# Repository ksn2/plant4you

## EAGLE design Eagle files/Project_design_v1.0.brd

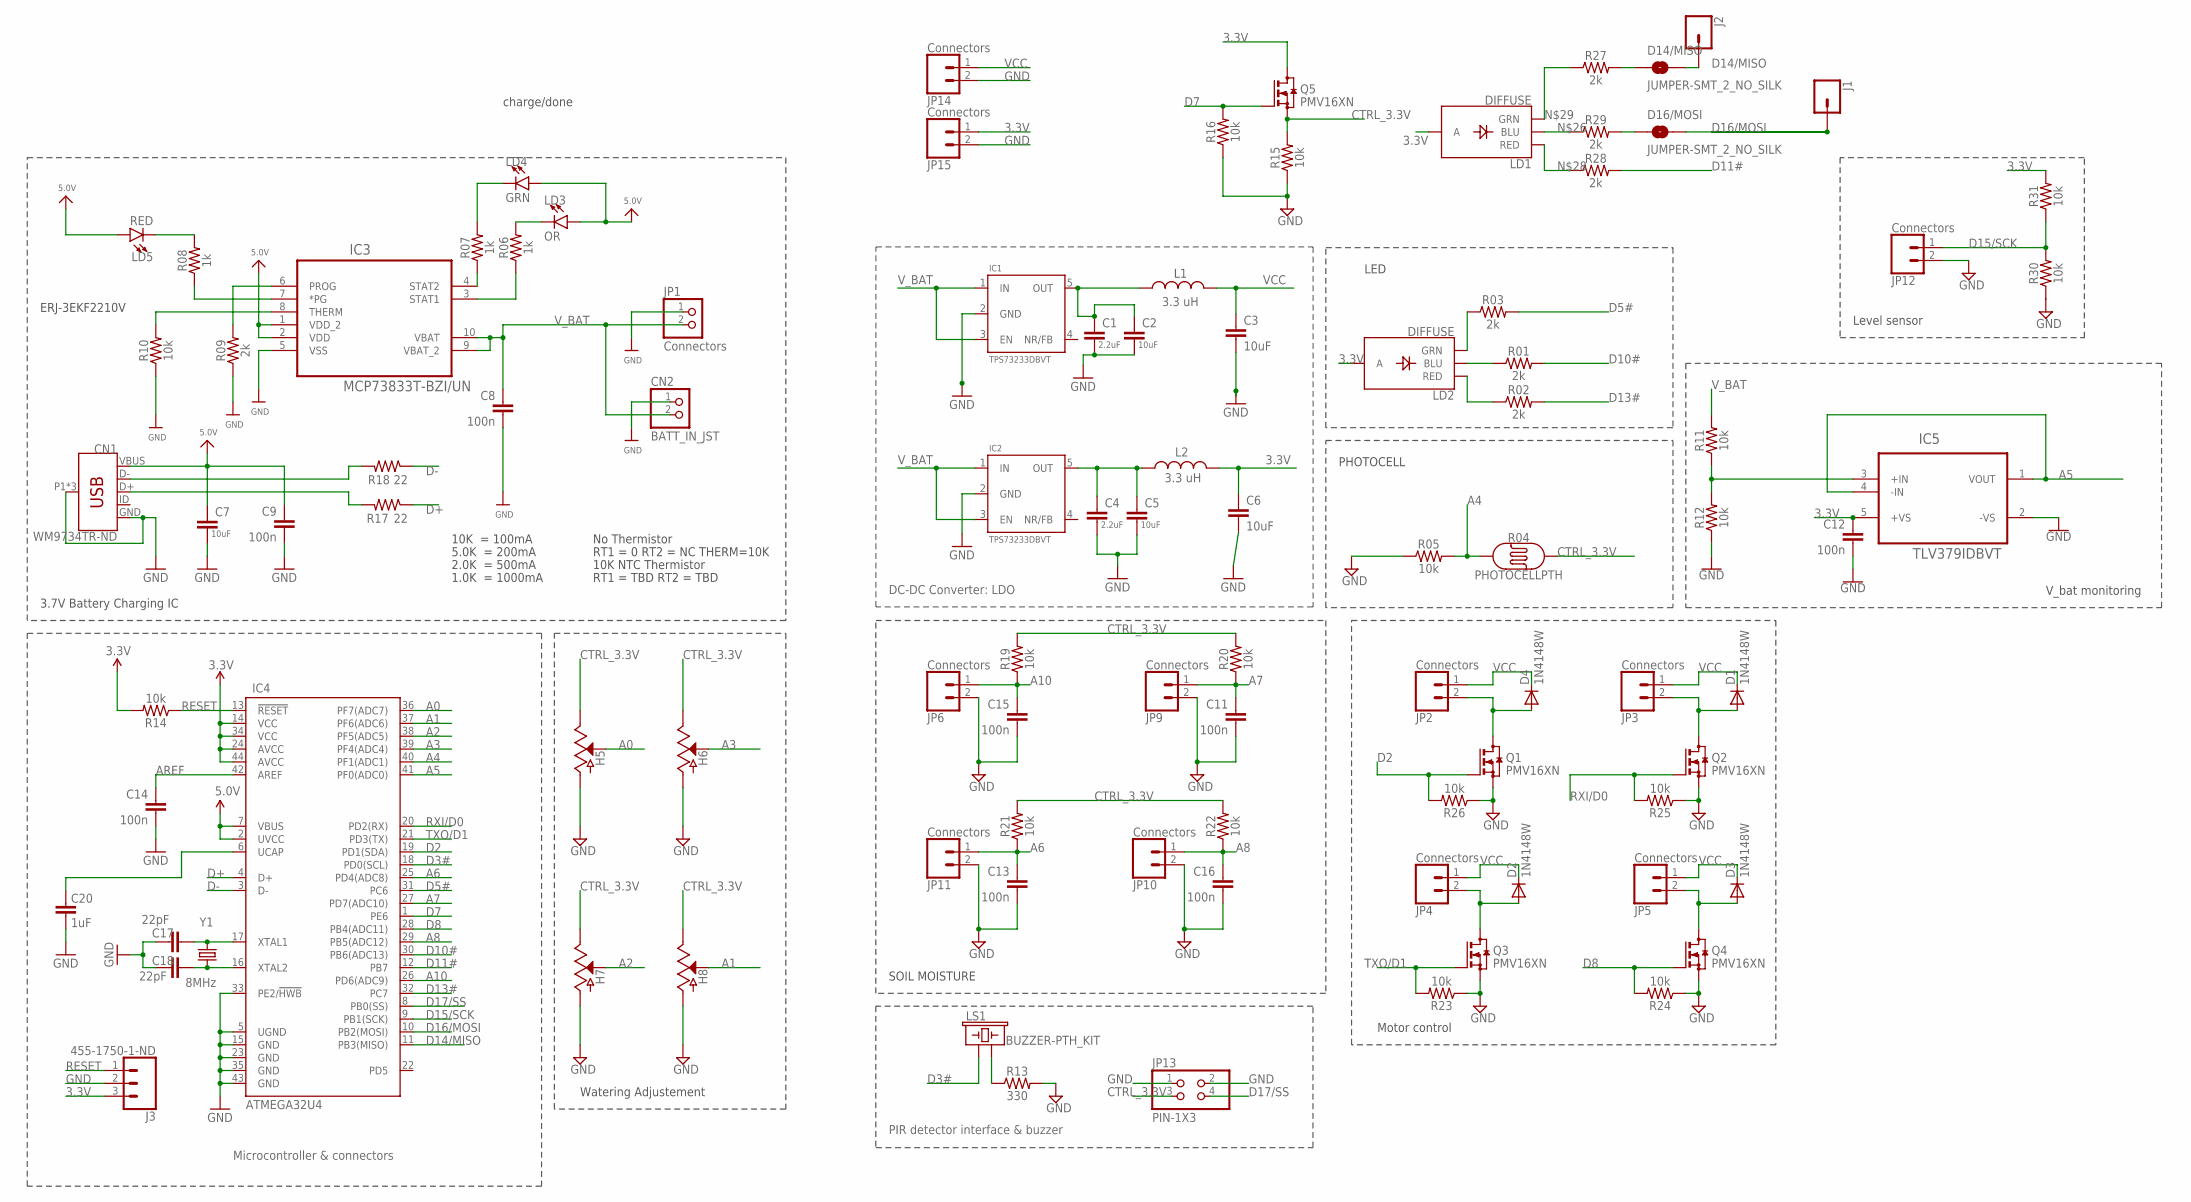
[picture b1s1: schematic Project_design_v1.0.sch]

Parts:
C1, C4: 2.2uF; 0603-CAP; PARTNO C1608X7S1C225K080AC
C2, C3, C5, C6, C7: 10uF; 0603-CAP; PARTNO GRM188R60J106ME47D
C8, C9, C11, C12, C13, C14, C15, C16: 100n; 0402; PARTNO CGA2B3X7R1E104K050BB
C17, C18: 22pF; 0603-CAP; PARTNO CL10C2R2BB8NNNC
C20: 1uF; 0603-CAP; PARTNO CL10B105KP8NNNC
CN1: WM9734TR-ND; USB-B-MICRO-SMD_VERT; PARTNO 1051330011
CN2: BATT_IN_JST; JSTPH2; PARTNO B2B-XH-A(LF)(SN)
D1, D2, D3, D4: 1N4148W; SOD-123_MINI-SMA; PARTNO 1N4148W
D14/MISO, D16/MOSI: JUMPER-SMT_2_NO_SILK; SMT-JUMPER_2_NO_SILK
H5: POT1; SOIL_MOISTURE; PARTNO SEN-13322
H6: POT2; SOIL_MOISTURE; PARTNO SEN-13322
H7: POT3; SOIL_MOISTURE; PARTNO SEN-13322
H8: POT4; SOIL_MOISTURE; PARTNO SEN-13322
IC1, IC2: TPS73233DBVT; SOT23-5; PARTNO TPS73233DBVT
IC3: MCP73833T-BZI/UN; SOP50P490X110-10N
IC4: ATMEGA32U4; TQFP44; PARTNO ATMEGA32U4RC-MUR
IC5: TLV379IDBVT; SOT95P280X145-5N; PARTNO TLV379IDBVT
J1, J2: CONN_01; 1X01
J3: 455-1750-1-ND; 1X03
JP1: Connectors; 1X02; PARTNO /
JP2, JP3, JP4, JP5, JP6, JP9, JP10, JP11, JP12, JP14, JP15: Connectors; 1X02; PARTNO M20-9960245
JP13: PIN-1X3; 2X02; PARTNO M22-2040805
L1, L2: 3.3 uH; 0603; PARTNO LQM18PN3R3MGHD
LD1, LD2: DIFFUSE; LED-RGB_THRU_5MM; PARTNO WP154A4SEJ3VBDZGW/CA
LD3: OR; LED_3MM; PARTNO TLHO4600
LD4: GRN; LED_3MM; PARTNO TLLG4400
LD5: RED; LED_3MM; PARTNO TLHK4600
LS1: BUZZER-PTH_KIT; BUZZER-12MM-KIT; PARTNO CEM-1203(42)
Q1, Q2, Q3, Q4, Q5: PMV16XN; SOT23; PARTNO PMV16XNR
R01, R02, R03, R09, R27, R28, R29: 2k; 0603; PARTNO ERJ-PA3F2001V
R04: PHOTOCELLPTH; PHOTOCELL; PARTNO 1528-2141-ND
R05, R10, R11, R12, R14, R15, R16, R19, R20, R21, R22, R23, R24, R25, R26, R30, R31: 10k; 0603; PARTNO ERA-3AEB103V
R06, R07, R08: 1k; 0603; PARTNO RC0603JR-07330RL
R13: 330; 0603; PARTNO RC0603JR-07330RL
R17, R18: 22; 0603-RES; PARTNO RC0603JR-0722RL
Y1: 8MHz; CRYSTAL-SMD-5X3; PARTNO ABM3C-8.000MHZ-D4Y-T

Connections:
3.3V: C6.1, C12.1, IC4.14 (VCC), IC4.24 (AVCC), IC4.34 (VCC), IC4.44 (AVCC), IC5.5 (+VS), J3.3, JP15.1, L2.2, LD1.3 (A), LD2.3 (A), Q5.3 (D), R14.2, R31.2
5.0V: C7.1, C9.1, CN1.VBUS, IC3.1 (VDD_2), IC3.2 (VDD), IC4.2 (UVCC), IC4.7 (VBUS), LD3.A, LD4.A, LD5.A
A0: H5.3 (VOUT), IC4.36 (PF7(ADC7))
A1: H8.3 (VOUT), IC4.37 (PF6(ADC6))
A2: H7.3 (VOUT), IC4.38 (PF5(ADC5))
A3: H6.3 (VOUT), IC4.39 (PF4(ADC4))
A4: IC4.40 (PF1(ADC1)), R04.1, R05.2
A5: IC4.41 (PF0(ADC0)), IC5.1 (VOUT), IC5.4 (-IN)
A6: C13.1, IC4.25 (PD4(ADC8)), JP11.1, R21.1
A7: C11.1, IC4.27 (PD7(ADC10)), JP9.1, R20.1
A8: C16.1, IC4.29 (PB5(ADC12)), JP10.1, R22.1
A10: C15.1, IC4.26 (PD6(ADC9)), JP6.1, R19.1
AREF: C14.1, IC4.42 (AREF)
CTRL_3.3V: H5.1 (VCC), H6.1 (VCC), H7.1 (VCC), H8.1 (VCC), JP13.3, Q5.2 (S), R04.2, R15.2, R19.2, R20.2, R21.2, R22.2
D2: IC4.19 (PD1(SDA)), Q1.1 (G), R26.2
D3#: IC4.18 (PD0(SCL)), LS1.+ (1)
D5#: IC4.31 (PC6), R03.2
D7: IC4.1 (PE6), Q5.1 (G), R16.2
D8: IC4.28 (PB4(ADC11)), Q4.1 (G), R24.2
D10#: IC4.30 (PB6(ADC13)), R01.2
D11#: IC4.12 (PB7), R28.2
D13#: IC4.32 (PC7), R02.2
D14/MISO: D14/MISO.2, IC4.11 (PB3(MISO)), J2.1
D15/SCK: IC4.9 (PB1(SCK)), JP12.1, R30.2, R31.1
D16/MOSI: D16/MOSI.2, IC4.10 (PB2(MOSI)), J1.1
D17/SS: IC4.8 (PB0(SS)), JP13.4
D+: IC4.4 (D+), R17.1
D-: IC4.3 (D-), R18.1
GND: C1.2, C2.2, C3.2, C4.2, C5.2, C6.2, C7.2, C8.2, C9.2, C11.2, C12.2, C13.2, C14.2, C15.2, C16.2, C17.2, C18.2, C20.1, CN1.GND, CN1.P1 (SHIELD), CN1.P2 (SHIELD), CN1.P3 (SHIELD), CN2.1, H5.2 (GND), H6.2 (GND), H7.2 (GND), H8.2 (GND), IC1.2 (GND), IC2.2 (GND), IC3.5 (VSS), IC4.5 (UGND), IC4.15 (GND), IC4.23 (GND), IC4.33 (PE2/!HWB), IC4.35 (GND), IC4.43 (GND), IC5.2 (-VS), J3.2, JP1.1, JP6.2, JP9.2, JP10.2, JP11.2, JP12.2, JP13.1, JP13.2, JP14.2, JP15.2, Q1.2 (S), Q2.2 (S), Q3.2 (S), Q4.2 (S), R05.1, R09.1, R10.1, R12.1, R13.2, R15.1, R16.1, R23.1, R24.1, R25.1, R26.1, R30.1
unnamed: LD2.2 (GRN), R03.1
unnamed: C4.1, C5.1, IC2.5 (OUT), L2.1
unnamed: LD3.K (C), R06.2
unnamed: LD4.K (C), R07.2
unnamed: IC3.4 (STAT2), R07.1
unnamed: IC3.3 (STAT1), R06.1
unnamed: IC3.7 (*PG), R08.1
unnamed: IC3.8 (THERM), R10.2
unnamed: C18.1, IC4.16 (XTAL2), Y1.1
unnamed: D4.A, JP2.2, Q1.3 (D)
unnamed: D1.A, JP3.2, Q2.3 (D)
unnamed: LD5.K (C), R08.2
unnamed: C1.1, C2.1, IC1.5 (OUT), L1.1
unnamed: D2.A, JP4.2, Q3.3 (D)
unnamed: D3.A, JP5.2, Q4.3 (D)
unnamed: IC3.6 (PROG), R09.2
unnamed: IC5.3 (+IN), R11.1, R12.2
unnamed: C17.1, IC4.17 (XTAL1), Y1.3 (2)
unnamed: C20.2, IC4.6 (UCAP)
unnamed: CN1.D-, R18.2
unnamed: CN1.D+, R17.2
unnamed: LS1.- (2), R13.1
unnamed: LD1.1 (BLU), R29.1
unnamed: LD1.4 (RED), R28.1
unnamed: LD1.2 (GRN), R27.1
unnamed: D16/MOSI.1, R29.2
unnamed: D14/MISO.1, R27.2
unnamed: LD2.1 (BLU), R01.1
unnamed: LD2.4 (RED), R02.1
RESET: IC4.13 (!RESET), J3.1, R14.1
RXI/D0: IC4.20 (PD2(RX)), Q2.1 (G), R25.2
TXO/D1: IC4.21 (PD3(TX)), Q3.1 (G), R23.2
VCC: C3.1, D1.C, D2.C, D3.C, D4.C, JP2.1, JP3.1, JP4.1, JP5.1, JP14.1, L1.2
V_BAT: C8.1, CN2.2, IC1.1 (IN), IC1.3 (EN), IC2.1 (IN), IC2.3 (EN), IC3.9 (VBAT_2), IC3.10 (VBAT), JP1.2, R11.2

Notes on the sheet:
LED
PHOTOCELL
SOIL MOISTURE
DC-DC Converter: LDO
10K = 100mA
5.0K = 200mA
2.0K = 500mA
1.0K = 1000mA
No Thermistor
RT1 = 0 RT2 = NC THERM=10K
10K NTC Thermistor
RT1 = TBD RT2 = TBD
3.7V Battery Charging IC
charge/done
Motor control
Level sensor
ERJ-3EKF2210V
Watering Adjustement
V_bat monitoring
Microcontroller & connectors
PIR detector interface & buzzer

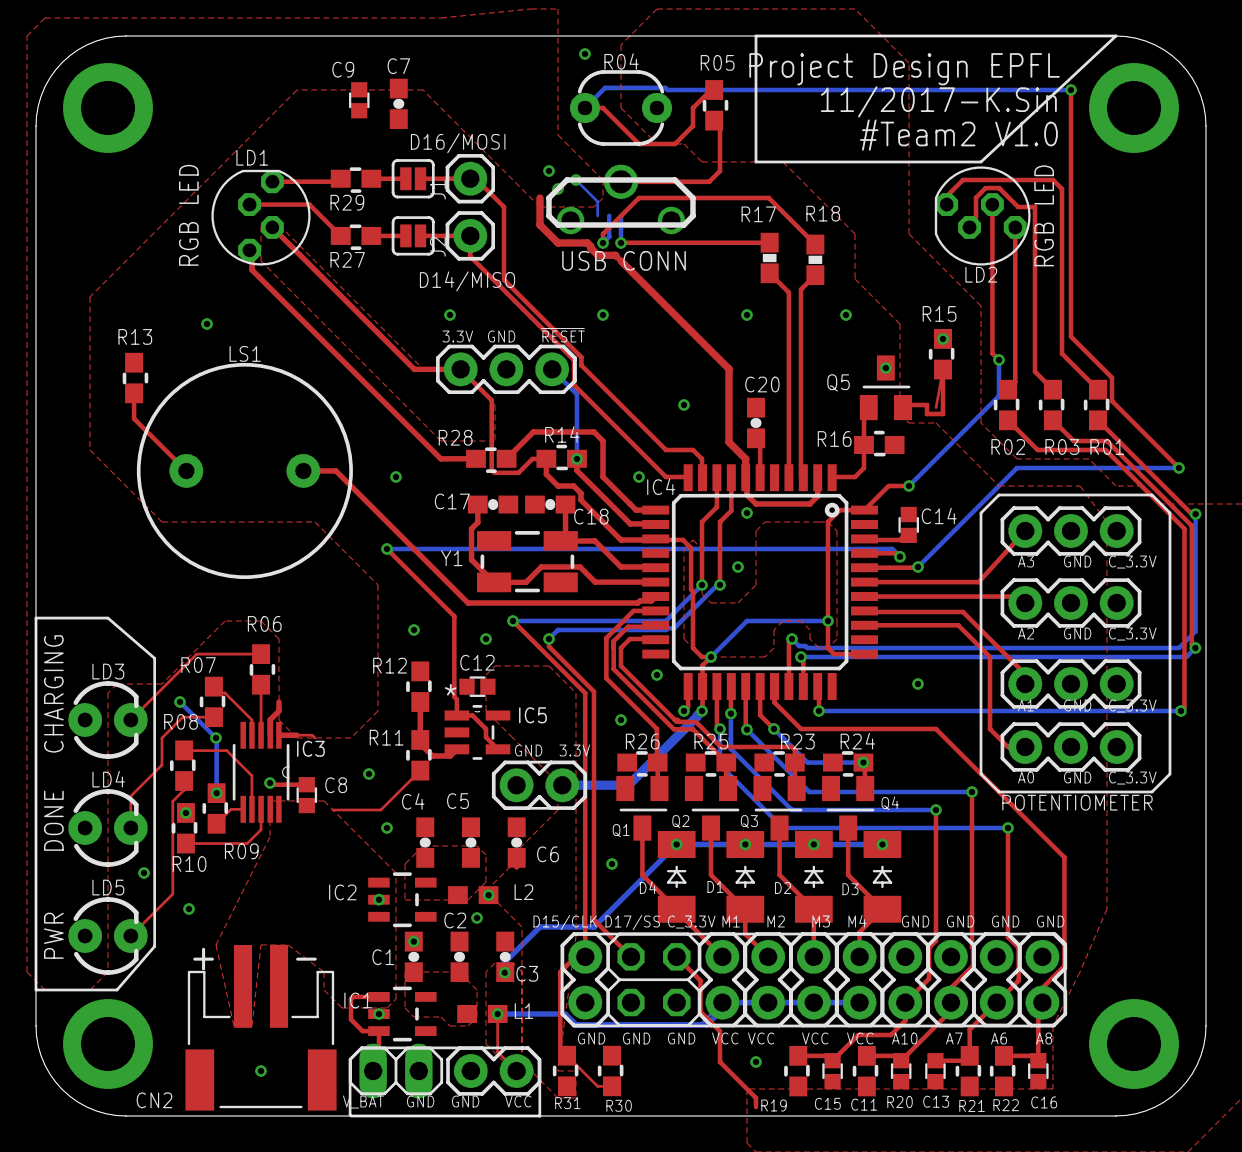
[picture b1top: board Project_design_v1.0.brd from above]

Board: 2 copper layers, 65.0 x 60.0 mm, 96 parts (1 on the bottom side), 63 nets.

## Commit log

2017-10-27 test
2017-10-27 doc de bellouard
2017-10-27 test2
2017-10-27 clean repository
2017-10-27 add readme
2017-10-27 eagle first schemattic;template for futur use
2017-10-30 passif components liste
2017-11-02 first arduino sketch added to control the birghtness of 1 LED
2017-11-02 code to drive a RGB LED added
2017-11-02 Guidelines for midterm presentation deleted
2017-11-02 Photocell code & Fading diode feedback
2017-11-02 Folder edited for the photocell project
2017-11-02 schematic des temperature, soil moisture, led, brightness sensor
2017-11-04 First arduino for the whole project: moisture sensors & motor;LEDs;analog reading of the birghtness sensor
2017-11-07 temperature sensor schmetatic & packages edited
2017-11-08 arduino code updated & correcter
2017-11-09 MCU, charging IC & power supply implemented on the eagle schematics
2017-11-09 corrections of few wire in the schematics
2017-11-12 part number & potentiometer to select the ammount of water needed for each pot
2017-11-14 add comments on components
2017-11-15 schematic almose finished, part number edited, and PIR & buzzer added
2017-11-16 schematics design uptaded and adjusted for exportation for the MS2
2017-11-24 bonojur
2017-11-25 PCB line + silkscreen updated
2017-11-29 final version of the PCB, final BOM, and .gitignore file added; let's start coding
2017-12-05 Update of the Arduino code, RGB LED class added, Library edited
2017-12-12 Arduino Code updated
2017-12-14 final code of the project
2017-12-18 final commit before presentation, I had fun

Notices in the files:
parts and their libraries:
SparkFun-Sensors: Licensing: Creative Commons ShareAlike 4.0 International - https://creativecommons.org/licenses/by-sa/4.0
SparkFun-Passives: Licensing: CC v3.0 Share-Alike You are welcome to use this library for commercial purposes.
